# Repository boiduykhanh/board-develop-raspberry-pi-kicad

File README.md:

# board-develop-raspberry-pi-kicad
Boad phát triển raspberey pi
## Tổng quan
### Sơ đồ nguyên lý

### PCB

### 3D

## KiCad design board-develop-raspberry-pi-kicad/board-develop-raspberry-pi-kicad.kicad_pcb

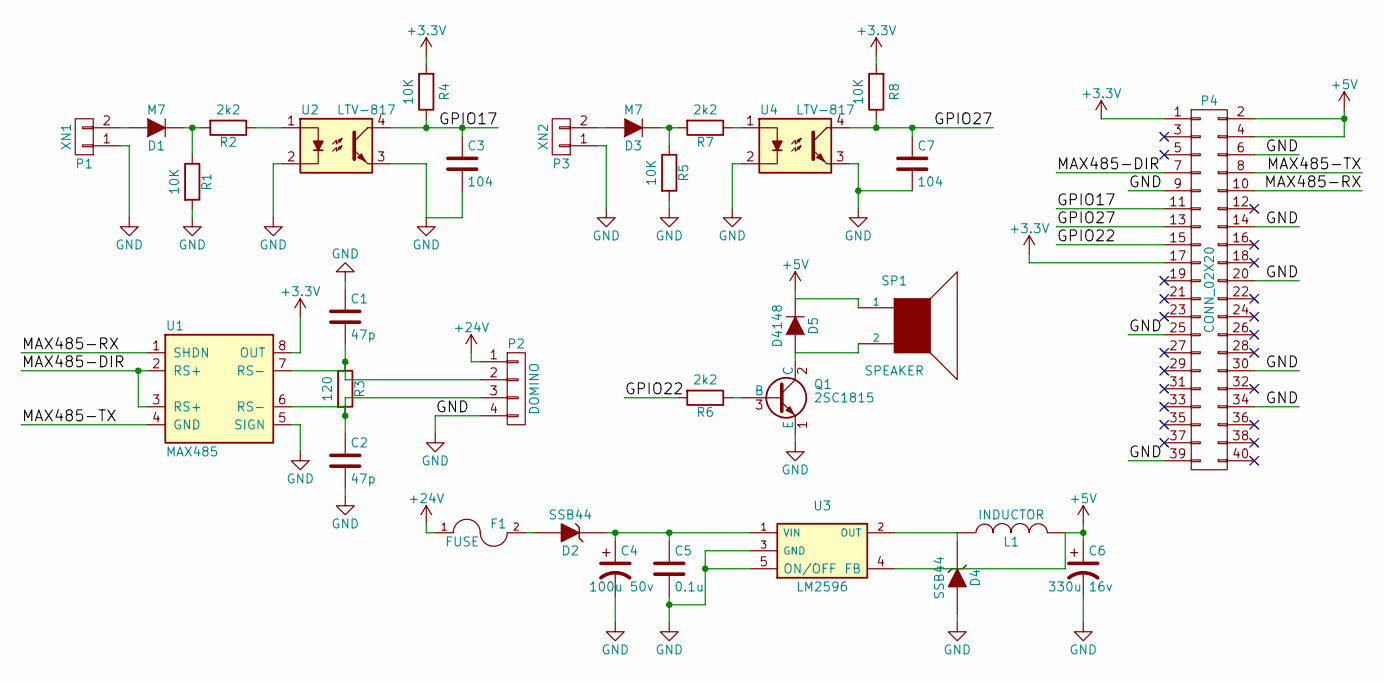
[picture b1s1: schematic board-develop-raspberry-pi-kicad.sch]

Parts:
C1, C2: 47p; C_0805_HandSoldering
C3, C7: 104; C_0805_HandSoldering
C4: 100u 50v; c_elec_10x10
C5: 0.1u; C_0805_HandSoldering
C6: 330u 16v; c_elec_8x10
D1, D3: M7; SOD-123
D2, D4: SSB44; SMA_Standard
D5: D4148; SOD-123
F1: FUSE; Fuse_SMD2920
L1: INDUCTOR; SELF-WE-PD-XXL
P1: XN1; domino-2
P2: DOMINO; Molex_KK_6410-04
P3: XN2; domino-2
P4: CONN_02X20; Pin_Header_Straight_2x20
Q1: 2SC1815; SOT-23
R1, R4, R5, R8: 10K; R_0805_HandSoldering
R2, R6, R7: 2k2; R_0805_HandSoldering
R3: 120; R_0805_HandSoldering
SP1: SPEAKER; BUZZER
U1: MAX485; SOIC-8_3.9x4.9mm_Pitch1.27mm
U2, U4: LTV-817; Optocoupler_SMD_HandSoldering_KPC357_LTV35x_PC357_SingleCha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
U3: LM2596; TO-263-5Lead

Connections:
+3V3: P4.1, P4.17, R4.2, R8.2, U1.8 (OUT)
+5V: C6.1, D5.1 (K), L1.2, P4.2, P4.4, SP1.1, U3.4 (FB)
+24V: F1.1, P2.1
/GPIO17: C3.1, P4.11, R4.1, U2.4
/GPIO22: P4.15, R6.2
/GPIO27: C7.1, P4.13, R8.1, U4.4
/MAX485-DIR: P4.7, U1.2 (RS+), U1.3 (RS+)
/MAX485-RX: P4.10, U1.1 (SHDN)
/MAX485-TX: P4.8, U1.4 (GND)
GND: C1.1, C2.2, C3.2, C4.2, C5.2, C6.2, C7.2, D4.2 (A), P1.1, P2.4, P3.1, P4.6, P4.9, P4.14, P4.20, P4.25, P4.30, P4.34, P4.39, Q1.1 (E), R1.2, R5.2, U1.5 (SIGN), U2.2, U2.3, U3.3 (GND), U3.5 (ON/OFF), U4.2, U4.3
unnamed: C1.2, P2.2, R3.1, U1.7 (RS-)
unnamed: C2.1, P2.3, R3.2, U1.6 (RS-)
unnamed: C4.1, C5.1, D2.1 (K), U3.1 (VIN)
unnamed: D1.1 (K), R1.1, R2.2
unnamed: D1.2 (A), P1.2
unnamed: D2.2 (A), F1.2
unnamed: D3.1 (K), R5.1, R7.2
unnamed: D3.2 (A), P3.2
unnamed: D4.1 (K), L1.1, U3.2 (OUT)
unnamed: D5.2 (A), Q1.2 (C), SP1.2
unnamed: Q1.3 (B), R6.1
unnamed: R2.1, U2.1
unnamed: R7.1, U4.1

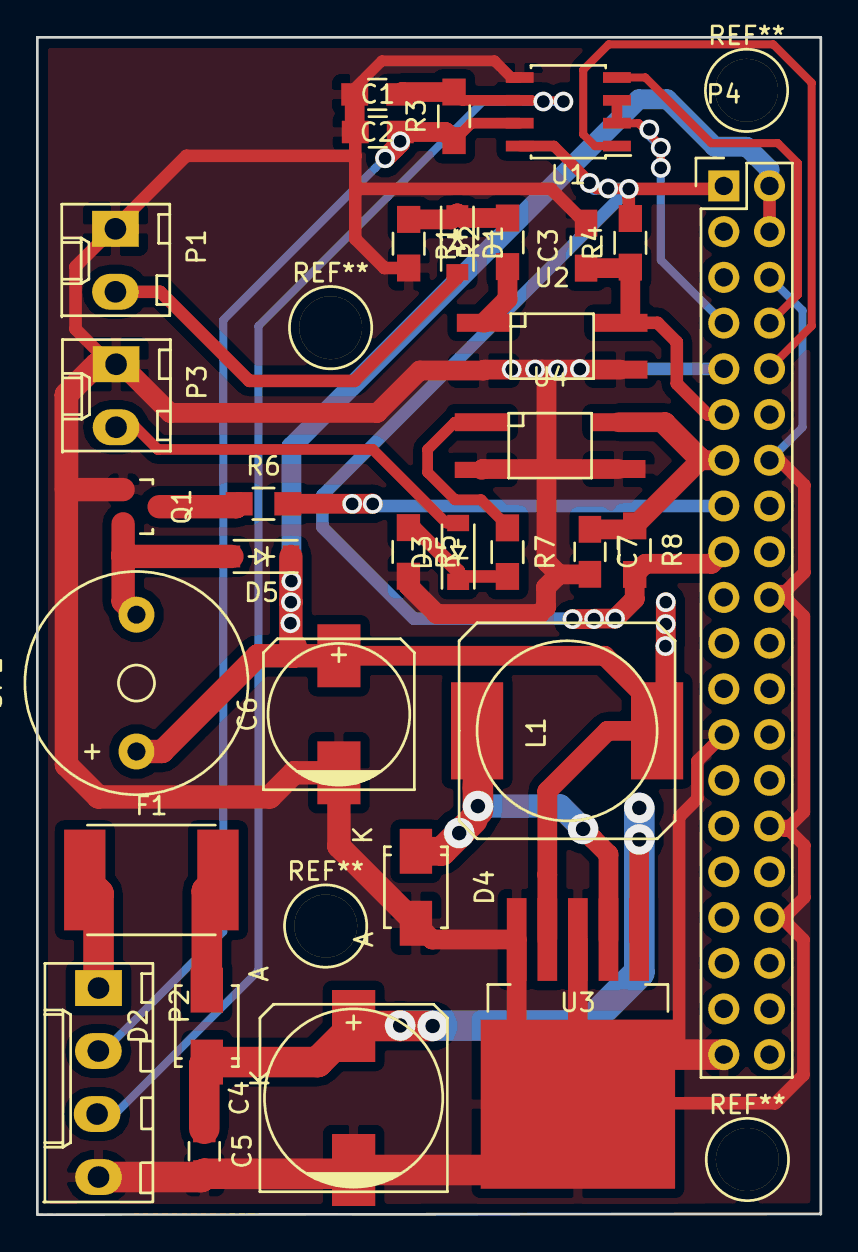
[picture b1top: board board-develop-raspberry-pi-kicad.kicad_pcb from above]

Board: 2 copper layers, 43.5 x 65.4 mm, 32 parts (0 on the bottom side), 23 nets.

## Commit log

2016-07-03 initial sch
2016-07-04 backup sch 1st
2016-07-05 backup PCB 1st
2016-07-05 finish project version 1
